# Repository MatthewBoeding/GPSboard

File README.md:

# GPS Board v3.0 r1.1

This board was designed for ECEN-435 at the University of Nebraska-Lincoln (Scott Campus).

## Connections

## Board

## Issues and Troubleshooting
Testing is underway with more updates to come.

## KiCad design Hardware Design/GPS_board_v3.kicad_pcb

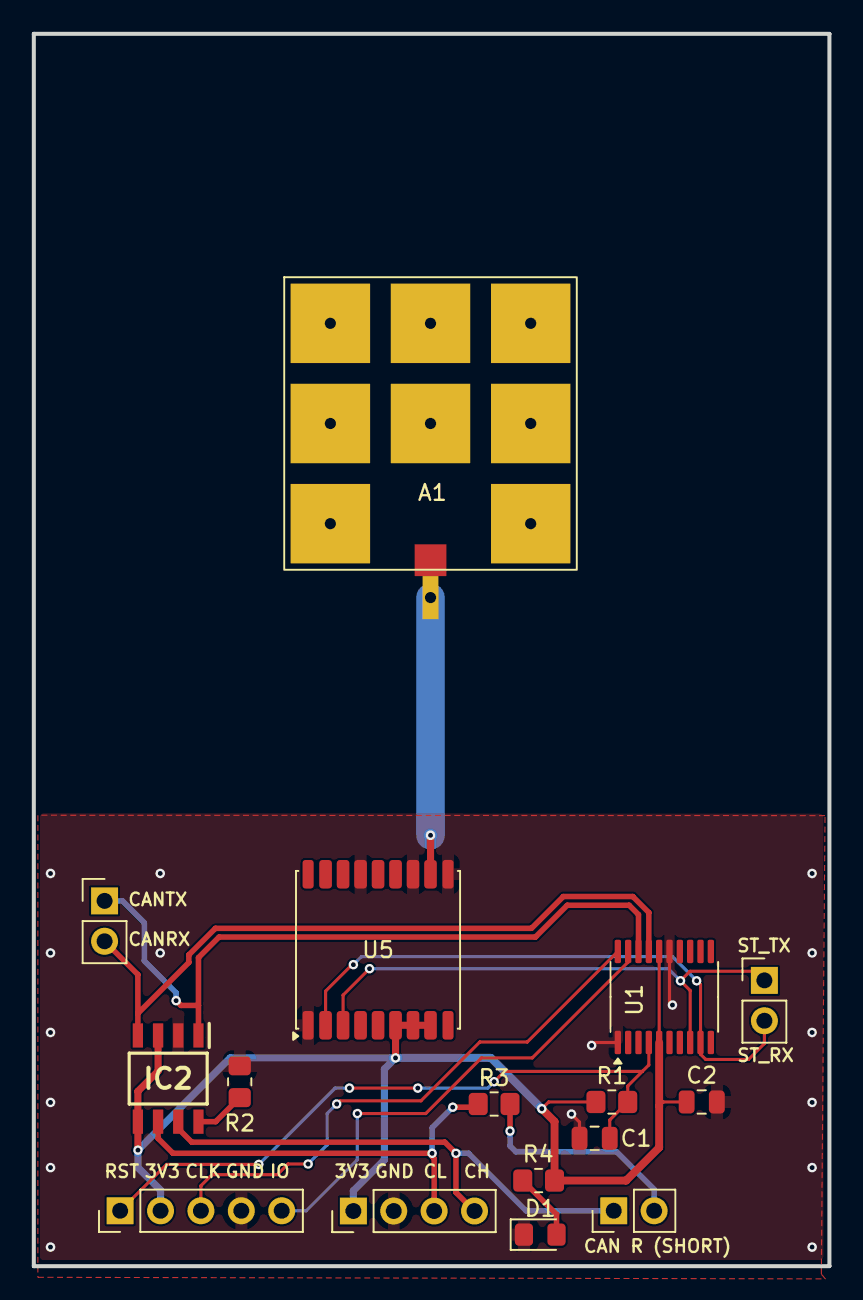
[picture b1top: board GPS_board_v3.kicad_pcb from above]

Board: 2 copper layers, 50.0 x 77.5 mm, 16 parts (0 on the bottom side), 15 nets.

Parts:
A1: L000953-01
C1, C2: .1uF; C_0805_2012Metric
D1: LED_Green; LED_0805_2012Metric_Pad1.15x1.40mm_HandSolder
IC2: SN65HVD231QDR; SOIC127P600X175-8N
J1, J5: STM-UART; PinHeader_1x02_P2.54mm_Vertical
J2: PinHeader_1x02_P2.54mm_Vertical
J3: PinHeader_1x04_P2.54mm_Vertical
J4: PinHeader_1x05_P2.54mm_Vertical
R1, R2: 10k; R_0805_2012Metric_Pad1.20x1.40mm_HandSolder
R3, R4: 120R; R_0805_2012Metric_Pad1.20x1.40mm_HandSolder
U1: STM32F042F4Px; TSSOP-20_4.4x6.5mm_P0.65mm
U5: MAX-M8W; ublox_MAX

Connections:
+3V3: C2.1, IC2.3 (VCC), IC2.5 (VREF), J3.1, J4.2, R1.1, R4.2, U1.5 (VDDA), U1.16 (VDD), U5.6 (V_BCKP), U5.7 (VCC_IO), U5.8 (VCC)
CANH: IC2.7 (CANH), J2.1, J3.4
CANL: IC2.6 (CANL), J3.3, R3.1
CAN_RX: IC2.4 (R), J5.2, U1.17 (PA9/PA11)
CAN_TX: IC2.1 (D), J5.1, U1.18 (PA10/PA12)
GND: A1.1 (GND), C1.2, C2.2, D1.1 (K), IC2.2 (GND), J3.2, J4.4, R2.2, U1.1 (PB8), U1.15 (VSSA), U5.1 (GND), U5.10 (GND), U5.12 (GND), U5.15 (V_ANT)
unnamed: A1.2 (RF_OUT), U5.11 (RF_IN)
unnamed: D1.2 (A), R4.1
unnamed: IC2.8 (RS), R2.1
unnamed: J2.2, R3.2
STM_RST: C1.1, J4.1, R1.2, U1.4 (NRST)
STM_UART_RX: J1.2, U1.9 (PA3), U5.2 (TXD)
STM_UART_TX: J1.1, U1.8 (PA2), U5.3 (RXD)
SWCLK: J4.3, U1.20 (PA14)
SWDIO: J4.5, U1.19 (PA13)

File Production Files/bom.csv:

Designator,Footprint,Quantity,Value,Man. Part #,Price $ (at 10 quantity),Mouser Link
A1,L000953-01,1,~,L000953-01,3.16,https://www.mouser.com/ProductDetail/TE-Connectivity-Linx-Te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
"C1, C2",805,2,.1uF,0805ZD104KAT2A,0.04,https://www.mouser.com/ProductDetail/KYOCERA-AVX/0805ZD104KA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
D1,805,1,LED_Green,LTST-S220GKT,0.095,https://www.mouser.com/ProductDetail/LITEON/LTST-S220GKT?qs=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
IC2,SOIC127P600X175-8N,1,SN65HVD231QDR,SN65HVD231QDR,2.63,https://www.mouser.com/ProductDetail/Texas-Instruments/SN65H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
"J1, J2",PinHeader_1x02_P2.54mm_Vertical,2,~,,,
J3,PinHeader_1x04_P2.54mm_Vertical,1,~,,,
J4,PinHeader_1x05_P2.54mm_Vertical,1,~,M20-9992046,0.589,https://www.mouser.com/ProductDetail/Harwin/M20-9992046?qs=%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
"R1, R2",805,2,10k,RT0805DRE0710KL,0.023,https://www.mouser.com/ProductDetail/YAGEO/RT0805DRE0710KL?q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
"R3, R4",805,2,120R,RT0805FRE13120RL,0.035,https://www.mouser.com/ProductDetail/YAGEO/RT0805FRE13120RL?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
U1,TSSOP-20_4.4x6.5mm_P0.65mm,1,STM32F042F4Px,STM32F042F4P6,2.14,https://www.mouser.com/ProductDetail/STMicroelectronics/STM3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
U5,ublox_MAX_gps,1,MAX-M8C,MAX-M8C-0,16.2,https://www.mouser.com/ProductDetail/u-blox/MAX-M8C-0?qs=DPo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
,,,,,,
,,,,,,
,,,,Price per student $ (at 10 board quantity):,24.58805,

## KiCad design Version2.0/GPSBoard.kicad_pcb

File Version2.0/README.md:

# GPS Board V2.0
This board was designed for ECEN-4350 at the University of Nebraska-Lincoln (Scott Campus), so I will not be updating once completed. 
If a new design is required in the future, I will place it here. 
R1-R3 = 1kΩ, L2 = 5.6nH, C1 = 0Ω, C2 = 1.8 pF, C3 = 1µF

## Connections

## Issues and Troubleshooting
Version 1.0 board had issues with CAN communication. If this design is reused, will need to add on an LDO and allow for 5.0V to troubleshoot CAN transmission errors.

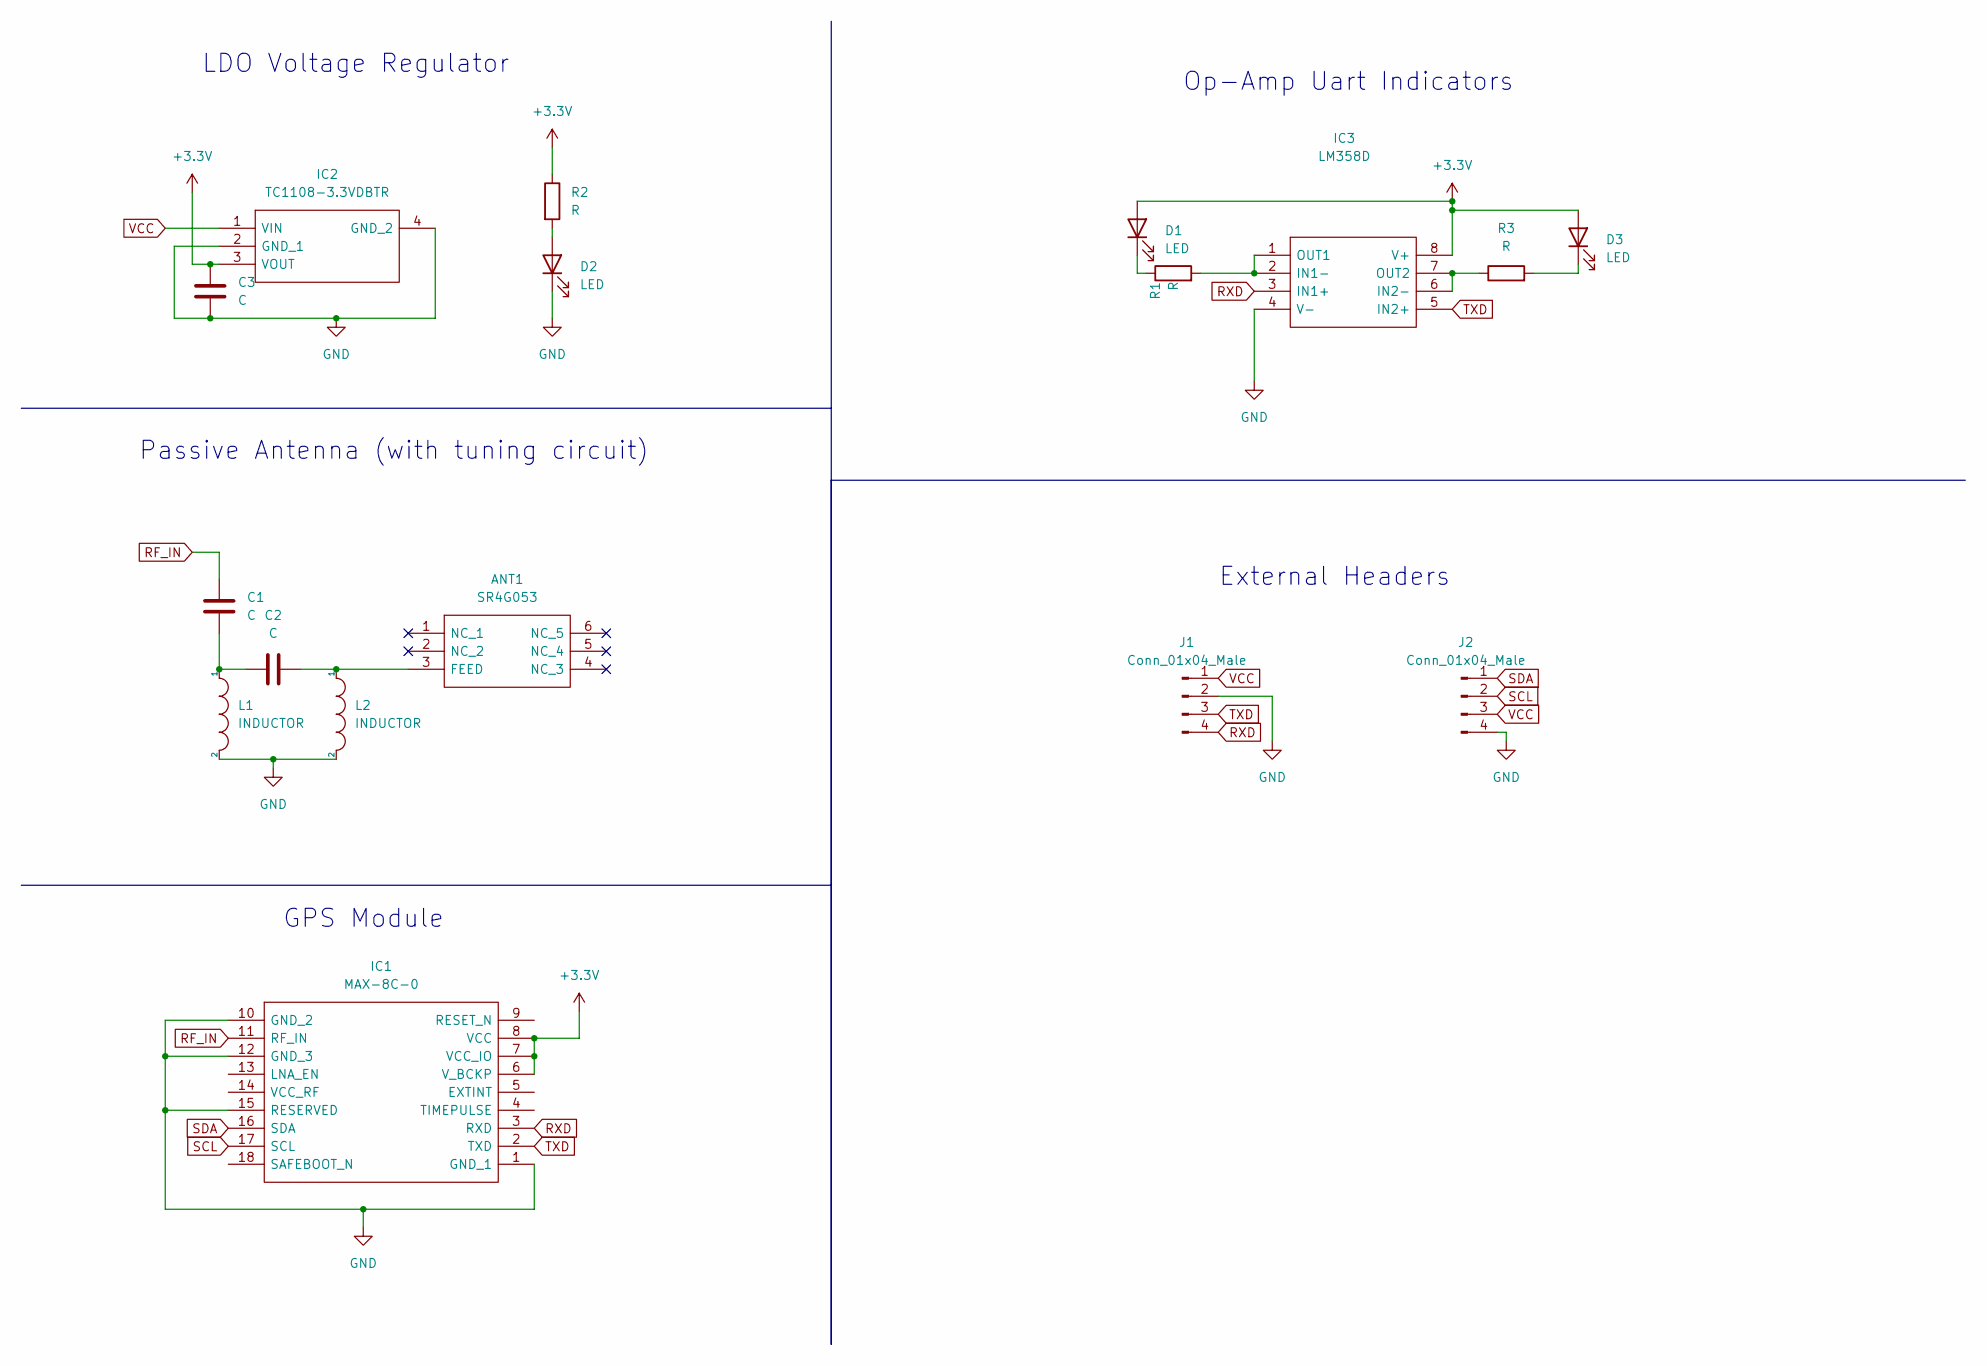
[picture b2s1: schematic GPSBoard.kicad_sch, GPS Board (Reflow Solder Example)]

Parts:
ANT1: SR4G053; Mouser Part Number 237-SR4G053
C1, C2, C3: C; R_0805_2012Metric
D1, D2, D3: LED; LED_0805_2012Metric
IC1: MAX-8C-0; MAX8C0; Mouser Part Number 377-MAX-8C-0
IC2: TC1108-3.3VDBTR; SOT230P700X180-4N; Mouser Part Number 579-TC1108-3.3VDBTR
IC3: LM358D; SOIC127P600X175-8N; Mouser Part Number 595-LM358D
J1, J2: Conn_01x04_Male; PinHeader_1x04_P2.54mm_Vertical
L1, L2: INDUCTOR; R_0805_2012Metric
R1, R2, R3: R; R_0805_2012Metric

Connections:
+3V3: C3.1, D1.2 (A), D3.2 (A), IC1.6 (V_BCKP), IC1.7 (VCC_IO), IC1.8 (VCC), IC2.3 (VOUT), IC3.8 (V+), R2.1
GND: C3.2, D2.1 (K), IC1.1 (GND_1), IC1.10 (GND_2), IC1.12 (GND_3), IC1.15 (RESERVED), IC2.2 (GND_1), IC2.4 (GND_2), IC3.4 (V-), J1.2, J2.4, L1.2, L2.2
unnamed: ANT1.3 (FEED), C2.2, L2.1
unnamed: C1.2, C2.1, L1.1
unnamed: D2.2 (A), R2.2
unnamed: D3.1 (K), R3.2
unnamed: IC3.1 (OUT1), IC3.2 (IN1-), R1.2
unnamed: IC3.6 (IN2-), IC3.7 (OUT2), R3.1
unnamed: D1.1 (K), R1.1
RF_IN: C1.1, IC1.11 (RF_IN)
RXD: IC1.3 (RXD), IC3.3 (IN1+), J1.4
SCL: IC1.17 (SCL), J2.2
SDA: IC1.16 (SDA), J2.1
TXD: IC1.2 (TXD), IC3.5 (IN2+), J1.3
VCC: IC2.1 (VIN), J1.1, J2.3

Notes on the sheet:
Passive Antenna (with tuning circuit)
GPS Module
LDO Voltage Regulator
Op-Amp Uart Indicators
External Headers

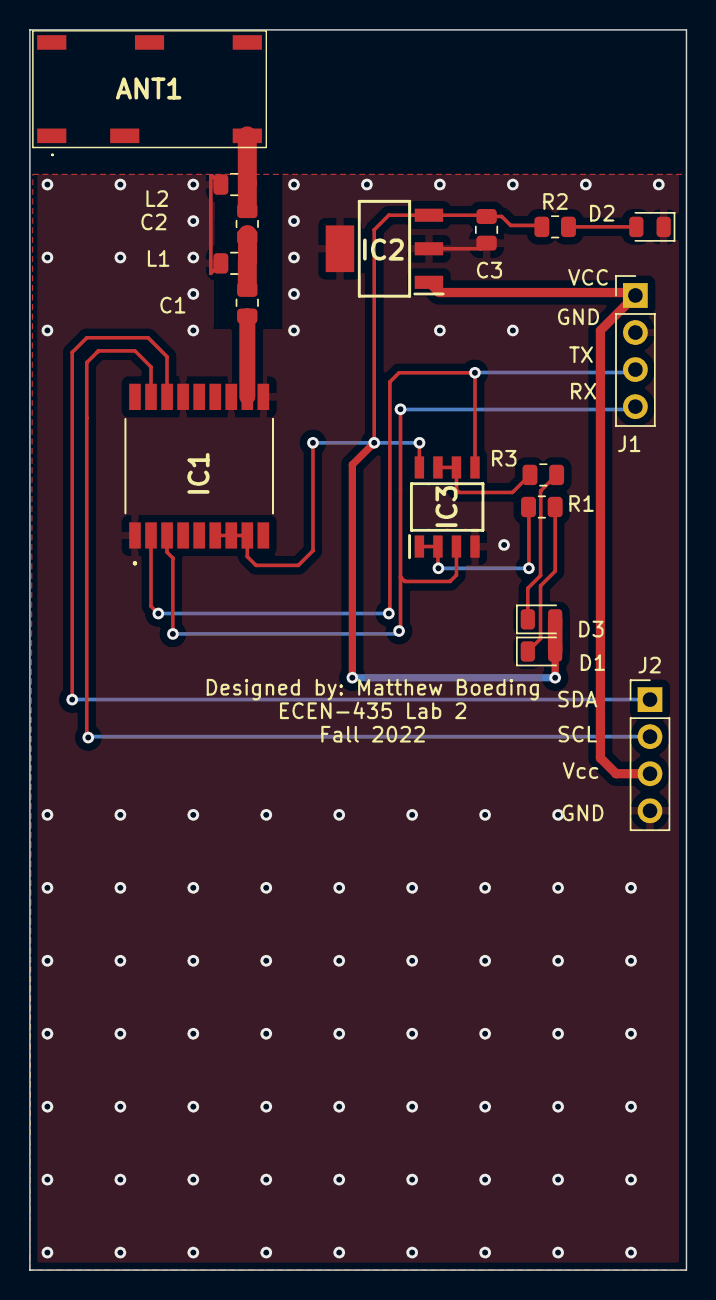
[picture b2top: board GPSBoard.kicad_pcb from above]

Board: 2 copper layers, 45.0 x 85.0 mm, 17 parts (0 on the bottom side), 15 nets.

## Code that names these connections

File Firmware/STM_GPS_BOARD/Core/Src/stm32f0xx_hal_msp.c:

/* USER CODE BEGIN Header */
/**
  ******************************************************************************
  * @file         stm32f0xx_hal_msp.c
  * @brief        This file provides code for the MSP Initialization
  *               and de-Initialization codes.
  ******************************************************************************
  * @attention
  *
  * Copyright (c) 2025 STMicroelectronics.
  * All rights reserved.
  *
  * This software is licensed under terms that can be found in the LICENSE file
  * in the root directory of this software component.
  * If no LICENSE file comes with this software, it is provided AS-IS.
  *
  ******************************************************************************
  */
/* USER CODE END Header */

/* Includes ------------------------------------------------------------------*/
#include "main.h"
/* USER CODE BEGIN Includes */

/* USER CODE END Includes */

/* Private typedef -----------------------------------------------------------*/
/* USER CODE BEGIN TD */

/* USER CODE END TD */

/* Private define ------------------------------------------------------------*/
/* USER CODE BEGIN Define */

/* USER CODE END Define */

/* Private macro -------------------------------------------------------------*/
/* USER CODE BEGIN Macro */

/* USER CODE END Macro */

/* Private variables ---------------------------------------------------------*/
/* USER CODE BEGIN PV */

/* USER CODE END PV */

/* Private function prototypes -----------------------------------------------*/
/* USER CODE BEGIN PFP */

/* USER CODE END PFP */

/* External functions --------------------------------------------------------*/
/* USER CODE BEGIN ExternalFunctions */

/* USER CODE END ExternalFunctions */

/* USER CODE BEGIN 0 */

/* USER CODE END 0 */
/**
  * Initializes the Global MSP.
  */
void HAL_MspInit(void)
{

  /* USER CODE BEGIN MspInit 0 */

  /* USER CODE END MspInit 0 */

  __HAL_RCC_SYSCFG_CLK_ENABLE();
  __HAL_RCC_PWR_CLK_ENABLE();

  /* System interrupt init*/

  __HAL_REMAP_PIN_ENABLE(HAL_REMAP_PA11_PA12);

  /* USER CODE BEGIN MspInit 1 */

  /* USER CODE END MspInit 1 */
}

/**
  * @brief CAN MSP Initialization
  * This function configures the hardware resources used in this example
  * @param hcan: CAN handle pointer
  * @retval None
  */
void HAL_CAN_MspInit(CAN_HandleTypeDef* hcan)
{
  GPIO_InitTypeDef GPIO_InitStruct = {0};
  if(hcan->Instance==CAN)
  {
    /* USER CODE BEGIN CAN_MspInit 0 */

    /* USER CODE END CAN_MspInit 0 */
    /* Peripheral clock enable */
    __HAL_RCC_CAN1_CLK_ENABLE();

    __HAL_RCC_GPIOA_CLK_ENABLE();
    /**CAN GPIO Configuration
    PA11     ------> CAN_RX
    PA12     ------> CAN_TX
    */
    GPIO_InitStruct.Pin = GPIO_PIN_11|GPIO_PIN_12;
    GPIO_InitStruct.Mode = GPIO_MODE_AF_PP;
    GPIO_InitStruct.Pull = GPIO_NOPULL;
    GPIO_InitStruct.Speed = GPIO_SPEED_FREQ_HIGH;
    GPIO_InitStruct.Alternate = GPIO_AF4_CAN;
    HAL_GPIO_Init(GPIOA, &GPIO_InitStruct);

    /* CAN interrupt Init */
    HAL_NVIC_SetPriority(CEC_CAN_IRQn, 0, 0);
    HAL_NVIC_EnableIRQ(CEC_CAN_IRQn);
    /* USER CODE BEGIN CAN_MspInit 1 */

    /* USER CODE END CAN_MspInit 1 */

  }

}

/**
  * @brief CAN MSP De-Initialization
  * This function freeze the hardware resources used in this example
  * @param hcan: CAN handle pointer
  * @retval None
  */
void HAL_CAN_MspDeInit(CAN_HandleTypeDef* hcan)
{
  if(hcan->Instance==CAN)
  {
    /* USER CODE BEGIN CAN_MspDeInit 0 */

    /* USER CODE END CAN_MspDeInit 0 */
    /* Peripheral clock disable */
    __HAL_RCC_CAN1_CLK_DISABLE();

    /**CAN GPIO Configuration
    PA11     ------> CAN_RX
    PA12     ------> CAN_TX
    */
    HAL_GPIO_DeInit(GPIOA, GPIO_PIN_11|GPIO_PIN_12);

    /* CAN interrupt DeInit */
    HAL_NVIC_DisableIRQ(CEC_CAN_IRQn);
    /* USER CODE BEGIN CAN_MspDeInit 1 */

    /* USER CODE END CAN_MspDeInit 1 */
  }

}

/**
  * @brief TIM_Base MSP Initialization
  * This function configures the hardware resources used in this example
  * @param htim_base: TIM_Base handle pointer
  * @retval None
  */
void HAL_TIM_Base_MspInit(TIM_HandleTypeDef* htim_base)
{
  if(htim_base->Instance==TIM14)
  {
    /* USER CODE BEGIN TIM14_MspInit 0 */

    /* USER CODE END TIM14_MspInit 0 */
    /* Peripheral clock enable */
    __HAL_RCC_TIM14_CLK_ENABLE();
    /* TIM14 interrupt Init */
    HAL_NVIC_SetPriority(TIM14_IRQn, 0, 0);
    HAL_NVIC_EnableIRQ(TIM14_IRQn);
    /* USER CODE BEGIN TIM14_MspInit 1 */

    /* USER CODE END TIM14_MspInit 1 */

  }

}

/**
  * @brief TIM_Base MSP De-Initialization
  * This function freeze the hardware resources used in this example
  * @param htim_base: TIM_Base handle pointer
  * @retval None
  */
void HAL_TIM_Base_MspDeInit(TIM_HandleTypeDef* htim_base)
{
  if(htim_base->Instance==TIM14)
  {
    /* USER CODE BEGIN TIM14_MspDeInit 0 */

    /* USER CODE END TIM14_MspDeInit 0 */
    /* Peripheral clock disable */
    __HAL_RCC_TIM14_CLK_DISABLE();

    /* TIM14 interrupt DeInit */
    HAL_NVIC_DisableIRQ(TIM14_IRQn);
    /* USER CODE BEGIN TIM14_MspDeInit 1 */

    /* USER CODE END TIM14_MspDeInit 1 */
  }

}

/**
  * @brief UART MSP Initialization
  * This function configures the hardware resources used in this example
  * @param huart: UART handle pointer
  * @retval None
  */
void HAL_UART_MspInit(UART_HandleTypeDef* huart)
{
  GPIO_InitTypeDef GPIO_InitStruct = {0};
  if(huart->Instance==USART2)
  {
    /* USER CODE BEGIN USART2_MspInit 0 */

    /* USER CODE END USART2_MspInit 0 */
    /* Peripheral clock enable */
    __HAL_RCC_USART2_CLK_ENABLE();

    __HAL_RCC_GPIOA_CLK_ENABLE();
    /**USART2 GPIO Configuration
    PA2     ------> USART2_TX
    PA3     ------> USART2_RX
    */
    GPIO_InitStruct.Pin = GPIO_PIN_2|GPIO_PIN_3;
    GPIO_InitStruct.Mode = GPIO_MODE_AF_PP;
    GPIO_InitStruct.Pull = GPIO_NOPULL;
    GPIO_InitStruct.Speed = GPIO_SPEED_FREQ_HIGH;
    GPIO_InitStruct.Alternate = GPIO_AF1_USART2;
    HAL_GPIO_Init(GPIOA, &GPIO_InitStruct);

    /* USER CODE BEGIN USART2_MspInit 1 */

    /* USER CODE END USART2_MspInit 1 */

  }

}

/**
  * @brief UART MSP De-Initialization
  * This function freeze the hardware resources used in this example
  * @param huart: UART handle pointer
  * @retval None
  */
void HAL_UART_MspDeInit(UART_HandleTypeDef* huart)
{
  if(huart->Instance==USART2)
  {
    /* USER CODE BEGIN USART2_MspDeInit 0 */

    /* USER CODE END USART2_MspDeInit 0 */
    /* Peripheral clock disable */
    __HAL_RCC_USART2_CLK_DISABLE();

    /**USART2 GPIO Configuration
    PA2     ------> USART2_TX
    PA3     ------> USART2_RX
    */
    HAL_GPIO_DeInit(GPIOA, GPIO_PIN_2|GPIO_PIN_3);

    /* USER CODE BEGIN USART2_MspDeInit 1 */

    /* USER CODE END USART2_MspDeInit 1 */
  }

}

/* USER CODE BEGIN 1 */

/* USER CODE END 1 */

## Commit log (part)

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2021-07-23 Initial framework started
    Can't download newest XC compiler, but last version appears to work
2021-07-23 Timer Hardware Testing
    Ready to start on LCD library as well.
2021-07-28 Reorg
2021-07-29 Ready for LCD test
    Will write the rest of the handler after GPS board is running.
2021-07-29 Fixed casting/mismatching data types
2021-07-29 SPI rework
2021-08-12 Console for debugging. NMEA frame processing
2021-08-16 use supplied CAN libraries
2021-09-22 Working Board
2021-09-22 Code Version Final
    PIC18F26Q84 working with MAX-M8W.
2021-09-22 Include Schematic
2021-09-22 Final Cleanup
2021-09-22 Repo Complete!
    Code is working. I do not plan to monitor or update this repo.
2022-09-22 Updated Version
2022-09-22 Schematic Annotation Issues
2025-07-03 init commit
2025-07-03 readme
2025-07-03 Create LICENSE
2025-07-03 add bom
2025-07-04 Preserve Old Version Assets
2025-07-31 redesigned board for STM32
2025-07-31 fixed gerbers & bom
2025-07-31 added photo
